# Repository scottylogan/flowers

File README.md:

# Boards

There are two boards using essentially the same schematic.

*basic* is about 1 inch square

*flower* is shaped like a flower

# Code

The code is in `code/flowers.ino`. While the board should work with
V-USB, the code doesn't use that yet.

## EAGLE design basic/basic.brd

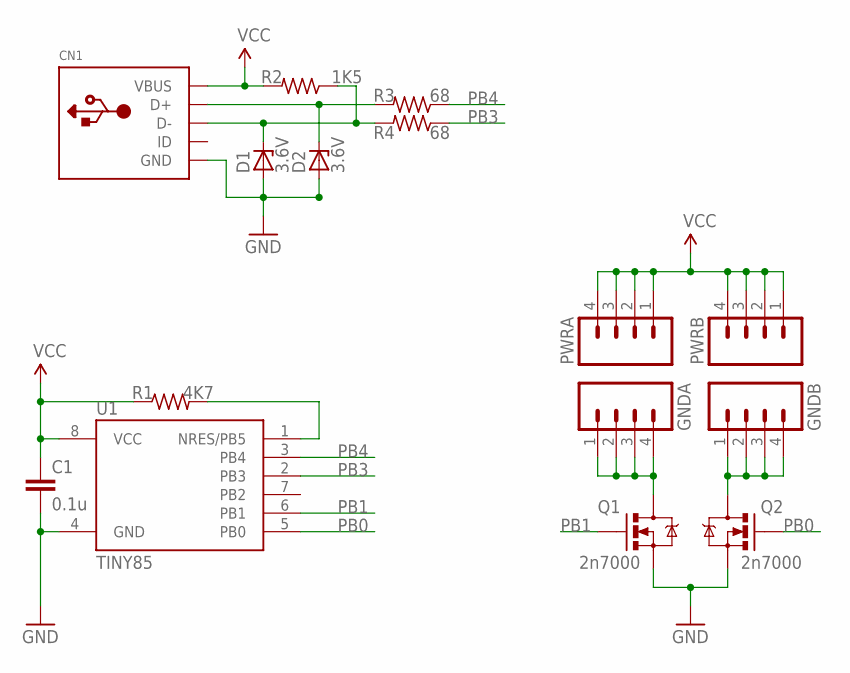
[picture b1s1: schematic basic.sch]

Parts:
C1: 0.1u; C025-024X044
CN1: USBMOLEX; USB-MINIB-THM-MOLEX
D1, D2: 3.6V; ZDIO-5
GNDA: M041X04_NO_SILK; 1X04_NO_SILK
GNDB: M041X04_NO_SILK; 1X04_NO_SILK
PWRA: M041X04_NO_SILK; 1X04_NO_SILK
PWRB: M041X04_NO_SILK; 1X04_NO_SILK
Q1, Q2: 2n7000; TO-92
R1: 4K7; 0204V
R2: 1K5; 0204V
R3, R4: 68; 0204V
U1: TINY85; PDIP08_300MIL

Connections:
D+: CN1.D+, D2.C, R3.2
D-: CN1.D-, D1.C, R2.1, R4.2
GND: C1.2, CN1.GND, D1.A, D2.A, Q1.1 (S), Q2.1 (S), U1.4 (GND)
unnamed: GNDA.1, GNDA.2, GNDA.3, GNDA.4, Q1.3 (D)
unnamed: R1.2, U1.1 (NRES/PB5)
unnamed: GNDB.1, GNDB.2, GNDB.3, GNDB.4, Q2.3 (D)
PB0: Q2.2 (G), U1.5 (PB0)
PB1: Q1.2 (G), U1.6 (PB1)
PB3: R4.1, U1.2 (PB3)
PB4: R3.1, U1.3 (PB4)
VCC: C1.1, CN1.VBUS, PWRA.1, PWRA.2, PWRA.3, PWRA.4, PWRB.1, PWRB.2, PWRB.3, PWRB.4, R1.1, R2.2, U1.8 (VCC)

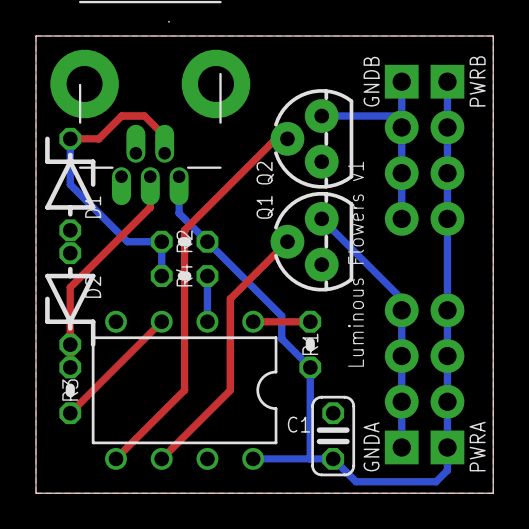
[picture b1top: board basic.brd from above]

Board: 2 copper layers, 25.4 x 25.4 mm, 15 parts (0 on the bottom side), 11 nets.

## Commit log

2019-04-25 added images
2019-04-25 resizing images
2019-04-25 reorganized files
2025-04-16 switched to MIT license

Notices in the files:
parts and their libraries:
SparkFun-Connectors: Licensing: Creative Commons ShareAlike 4.0 International - https://creativecommons.org/licenses/by-sa/4.0
